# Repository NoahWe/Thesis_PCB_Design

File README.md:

# Experiment
This repository contains the PCB designs for a pressure sensor array using BMP581 sensors which will be used during an experiment as part of my MSc thesis. The experiment aims to determine the pressure distribution over a wing, located behind tilting rotors. The sensor array is specifically aimed at the vehicle designed by Alessandro Mancinelli (https://doi.org/10.1109/ICUAS54217.2022.9836063), and is supposed to resolve some of the problems experienced using tilt-rotors to roll.

## How to get started
1. Clone the repository
2. Open one of the KiCad project files (.kicad_pro).

The mainboard is located in /Experiment_PCB/MainBoard/. The sensor strips connected to the top half of the wing are located in Experiment_PCB/SensorStrip_Top/, and finally the sensor strip connected to the bottom half of the wing are located in /Experiment_PCB/SensorStrip_Bottom/.

## Sensors
The sensor which will be used for the experiment is the BMP581: https://www.bosch-sensortec.com/products/environmental-sensors/pressure-sensors/bmp581/

The setup will have 72 pressure sensors which will be driven by a single Teensy4.1 board (https://www.pjrc.com/store/teensy41.html). The Teensy4.1 features 2 SPI buses allowing me to use a single chip select line to drive two sensors. The SPI buses will run at approximately 5 MHz.

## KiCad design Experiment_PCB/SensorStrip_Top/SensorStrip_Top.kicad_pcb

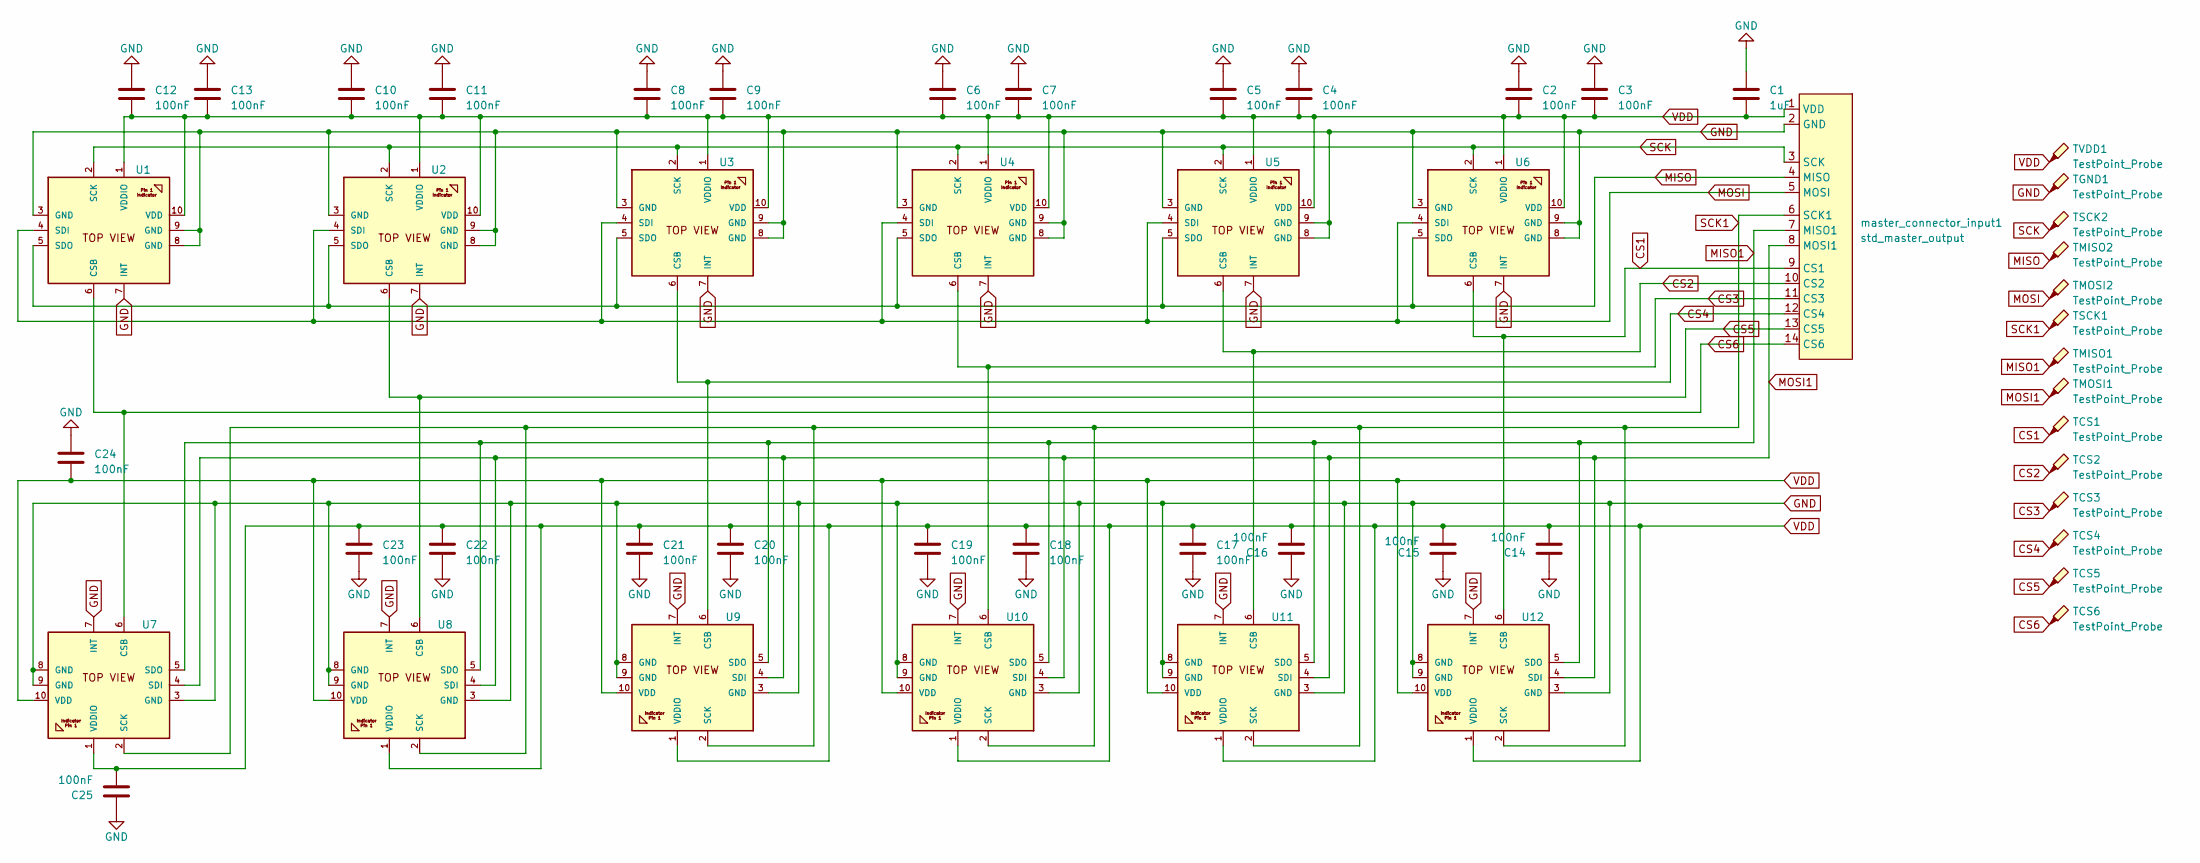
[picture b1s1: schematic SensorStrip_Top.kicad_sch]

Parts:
C1: 1uF; C_0603_1608Metric
C2, C3, C4, C5, C6, C7, C8, C9, C10, C11, C12, C13, C14, C15, C16, C17, C18, C19, C20, C21, C22, C23, C24, C25: 100nF; C_0201_0603Metric
TCS1, TCS2, TCS3, TCS4, TCS5, TCS6: TestPoint_Probe; TestPoint_Pad_1.0x1.0mm
TGND1: TestPoint_Probe; TestPoint_Pad_1.0x1.0mm
TMISO1, TMISO2: TestPoint_Probe; TestPoint_Pad_1.0x1.0mm
TMOSI1, TMOSI2: TestPoint_Probe; TestPoint_Pad_1.0x1.0mm
TSCK1, TSCK2: TestPoint_Probe; TestPoint_Pad_1.0x1.0mm
TVDD1: TestPoint_Probe; TestPoint_Pad_1.0x1.0mm
U1, U2, U3, U4, U5, U6, U7, U8, U9, U10, U11, U12: BMP581_Landing_Pattern
master_connector_input1: std_master_output; Strip_pins_top

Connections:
CS1: TCS1.1, U6.6 (CSB), U12.6 (CSB), master_connector_input1.9 (CS1)
CS2: TCS2.1, U5.6 (CSB), U11.6 (CSB), master_connector_input1.10 (CS2)
CS3: TCS3.1, U4.6 (CSB), U10.6 (CSB), master_connector_input1.11 (CS3)
CS4: TCS4.1, U3.6 (CSB), U9.6 (CSB), master_connector_input1.12 (CS4)
CS5: TCS5.1, U2.6 (CSB), U8.6 (CSB), master_connector_input1.13 (CS5)
CS6: TCS6.1, U1.6 (CSB), U7.6 (CSB), master_connector_input1.14 (CS6)
GND: C1.1, C2.1, C3.1, C4.1, C5.1, C6.1, C7.1, C8.1, C9.1, C10.1, C11.1, C12.1, C13.1, C14.1, C15.1, C16.1, C17.1, C18.1, C19.1, C20.1, C21.1, C22.1, C23.1, C24.1, C25.1, TGND1.1, U1.3 (GND), U1.7 (INT), U1.8 (GND), U1.9 (GND), U2.3 (GND), U2.7 (INT), U2.8 (GND), U2.9 (GND), U3.3 (GND), U3.7 (INT), U3.8 (GND), U3.9 (GND), U4.3 (GND), U4.7 (INT), U4.8 (GND), U4.9 (GND), U5.3 (GND), U5.7 (INT), U5.8 (GND), U5.9 (GND), U6.3 (GND), U6.7 (INT), U6.8 (GND), U6.9 (GND), U7.3 (GND), U7.7 (INT), U7.8 (GND), U7.9 (GND), U8.3 (GND), U8.7 (INT), U8.8 (GND), U8.9 (GND), U9.3 (GND), U9.7 (INT), U9.8 (GND), U9.9 (GND), U10.3 (GND), U10.7 (INT), U10.8 (GND), U10.9 (GND), U11.3 (GND), U11.7 (INT), U11.8 (GND), U11.9 (GND), U12.3 (GND), U12.7 (INT), U12.8 (GND), U12.9 (GND), master_connector_input1.2 (GND)
MISO: TMISO2.1, U1.5 (SDO), U2.5 (SDO), U3.5 (SDO), U4.5 (SDO), U5.5 (SDO), U6.5 (SDO), master_connector_input1.4 (MISO)
MISO1: TMISO1.1, U7.5 (SDO), U8.5 (SDO), U9.5 (SDO), U10.5 (SDO), U11.5 (SDO), U12.5 (SDO), master_connector_input1.7 (MISO1)
MOSI: TMOSI2.1, U1.4 (SDI), U2.4 (SDI), U3.4 (SDI), U4.4 (SDI), U5.4 (SDI), U6.4 (SDI), master_connector_input1.5 (MOSI)
MOSI1: TMOSI1.1, U7.4 (SDI), U8.4 (SDI), U9.4 (SDI), U10.4 (SDI), U11.4 (SDI), U12.4 (SDI), master_connector_input1.8 (MOSI1)
SCK: TSCK2.1, U1.2 (SCK), U2.2 (SCK), U3.2 (SCK), U4.2 (SCK), U5.2 (SCK), U6.2 (SCK), master_connector_input1.3 (SCK)
SCK1: TSCK1.1, U7.2 (SCK), U8.2 (SCK), U9.2 (SCK), U10.2 (SCK), U11.2 (SCK), U12.2 (SCK), master_connector_input1.6 (SCK1)
VDD: C1.2, C2.2, C3.2, C4.2, C5.2, C6.2, C7.2, C8.2, C9.2, C10.2, C11.2, C12.2, C13.2, C14.2, C15.2, C16.2, C17.2, C18.2, C19.2, C20.2, C21.2, C22.2, C23.2, C24.2, C25.2, TVDD1.1, U1.1 (VDDIO), U1.10 (VDD), U2.1 (VDDIO), U2.10 (VDD), U3.1 (VDDIO), U3.10 (VDD), U4.1 (VDDIO), U4.10 (VDD), U5.1 (VDDIO), U5.10 (VDD), U6.1 (VDDIO), U6.10 (VDD), U7.1 (VDDIO), U7.10 (VDD), U8.1 (VDDIO), U8.10 (VDD), U9.1 (VDDIO), U9.10 (VDD), U10.1 (VDDIO), U10.10 (VDD), U11.1 (VDDIO), U11.10 (VDD), U12.1 (VDDIO), U12.10 (VDD), master_connector_input1.1 (VDD)

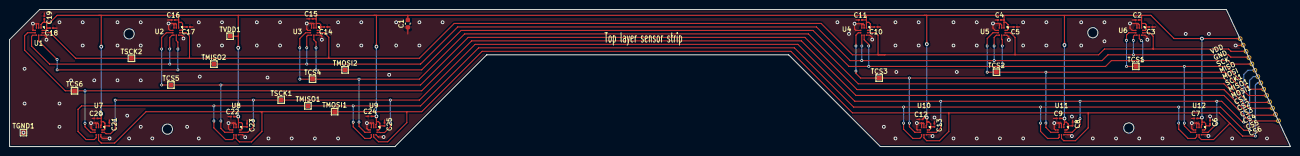
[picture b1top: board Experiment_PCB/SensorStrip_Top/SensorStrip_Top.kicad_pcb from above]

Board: 2 copper layers, 275.8 x 29.5 mm, 52 parts (0 on the bottom side), 14 nets.

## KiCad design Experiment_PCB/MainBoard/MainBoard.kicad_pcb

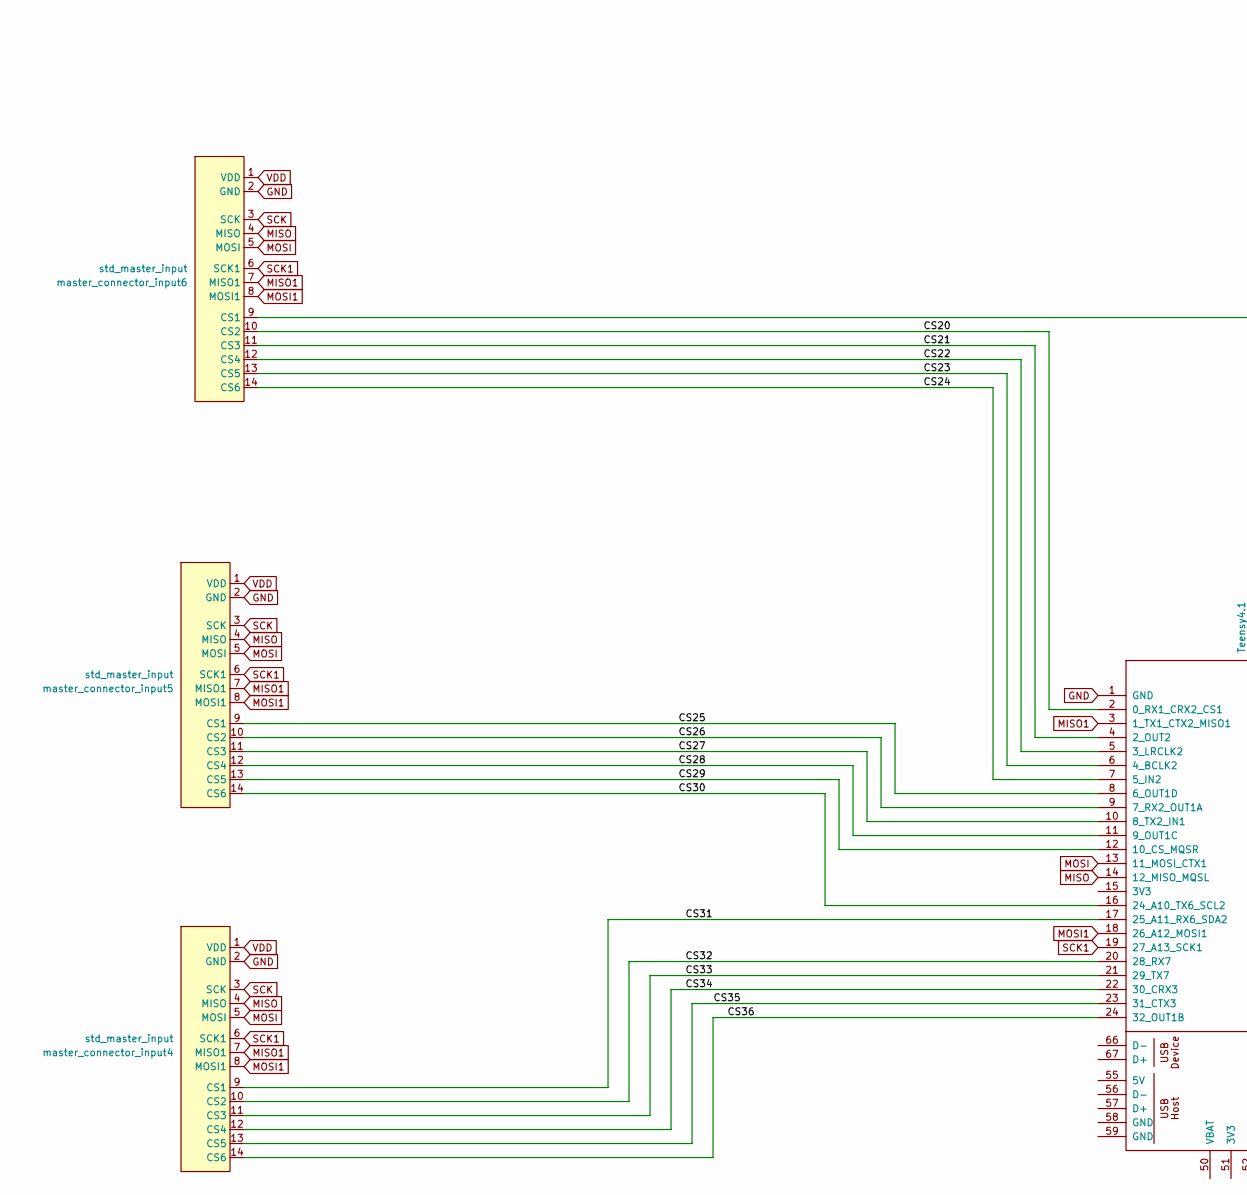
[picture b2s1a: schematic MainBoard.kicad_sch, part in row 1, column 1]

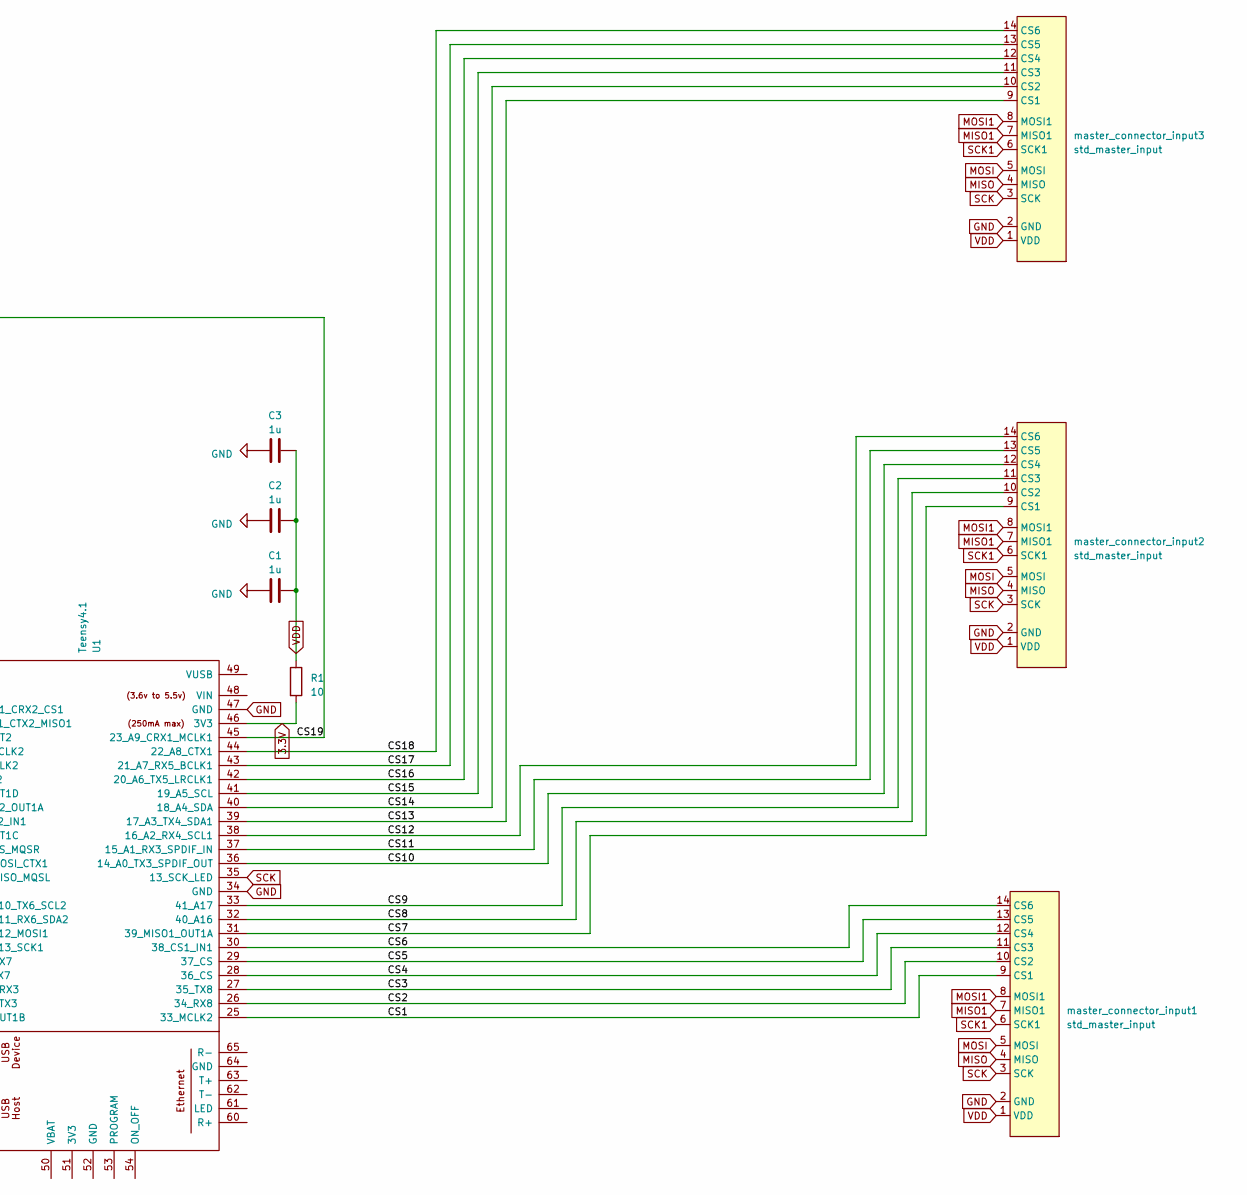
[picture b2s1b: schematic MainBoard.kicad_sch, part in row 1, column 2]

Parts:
C1, C2, C3: 1u; C_0603_1608Metric
R1: 10; R_0402_1005Metric
U1: Teensy4.1; Teensy41
master_connector_input1, master_connector_input3, master_connector_input5: std_master_input; Master_pins_top
master_connector_input2, master_connector_input4, master_connector_input6: std_master_input; Master_pins_bottom

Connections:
3.3V: R1.2, U1.46 (3V3)
/CS1: U1.25 (33_MCLK2), master_connector_input1.9 (CS1)
/CS2: U1.26 (34_RX8), master_connector_input1.10 (CS2)
/CS3: U1.27 (35_TX8), master_connector_input1.11 (CS3)
/CS4: U1.28 (36_CS), master_connector_input1.12 (CS4)
/CS5: U1.29 (37_CS), master_connector_input1.13 (CS5)
/CS6: U1.30 (38_CS1_IN1), master_connector_input1.14 (CS6)
/CS7: U1.31 (39_MISO1_OUT1A), master_connector_input2.9 (CS1)
/CS8: U1.32 (40_A16), master_connector_input2.10 (CS2)
/CS9: U1.33 (41_A17), master_connector_input2.11 (CS3)
/CS10: U1.36 (14_A0_TX3_SPDIF_OUT), master_connector_input2.12 (CS4)
/CS11: U1.37 (15_A1_RX3_SPDIF_IN), master_connector_input2.13 (CS5)
/CS12: U1.38 (16_A2_RX4_SCL1), master_connector_input2.14 (CS6)
/CS13: U1.39 (17_A3_TX4_SDA1), master_connector_input3.9 (CS1)
/CS14: U1.40 (18_A4_SDA), master_connector_input3.10 (CS2)
/CS15: U1.41 (19_A5_SCL), master_connector_input3.11 (CS3)
/CS16: U1.42 (20_A6_TX5_LRCLK1), master_connector_input3.12 (CS4)
/CS17: U1.43 (21_A7_RX5_BCLK1), master_connector_input3.13 (CS5)
/CS18: U1.44 (22_A8_CTX1), master_connector_input3.14 (CS6)
/CS19: U1.45 (23_A9_CRX1_MCLK1), master_connector_input6.9 (CS1)
/CS20: U1.2 (0_RX1_CRX2_CS1), master_connector_input6.10 (CS2)
/CS21: U1.4 (2_OUT2), master_connector_input6.11 (CS3)
/CS22: U1.5 (3_LRCLK2), master_connector_input6.12 (CS4)
/CS23: U1.6 (4_BCLK2), master_connector_input6.13 (CS5)
/CS24: U1.7 (5_IN2), master_connector_input6.14 (CS6)
/CS25: U1.8 (6_OUT1D), master_connector_input5.9 (CS1)
/CS26: U1.9 (7_RX2_OUT1A), master_connector_input5.10 (CS2)
/CS27: U1.10 (8_TX2_IN1), master_connector_input5.11 (CS3)
/CS28: U1.11 (9_OUT1C), master_connector_input5.12 (CS4)
/CS29: U1.12 (10_CS_MQSR), master_connector_input5.13 (CS5)
/CS30: U1.16 (24_A10_TX6_SCL2), master_connector_input5.14 (CS6)
/CS31: U1.17 (25_A11_RX6_SDA2), master_connector_input4.9 (CS1)
/CS32: U1.20 (28_RX7), master_connector_input4.10 (CS2)
/CS33: U1.21 (29_TX7), master_connector_input4.11 (CS3)
/CS34: U1.22 (30_CRX3), master_connector_input4.12 (CS4)
/CS35: U1.23 (31_CTX3), master_connector_input4.13 (CS5)
/CS36: U1.24 (32_OUT1B), master_connector_input4.14 (CS6)
GND: C1.1, C2.1, C3.1, U1.1 (GND), U1.34 (GND), U1.47 (GND), master_connector_input1.2 (GND), master_connector_input2.2 (GND), master_connector_input3.2 (GND), master_connector_input4.2 (GND), master_connector_input5.2 (GND), master_connector_input6.2 (GND)
MISO: U1.14 (12_MISO_MQSL), master_connector_input1.4 (MISO), master_connector_input2.4 (MISO), master_connector_input3.4 (MISO), master_connector_input4.4 (MISO), master_connector_input5.4 (MISO), master_connector_input6.4 (MISO)
MISO1: U1.3 (1_TX1_CTX2_MISO1), master_connector_input1.7 (MISO1), master_connector_input2.7 (MISO1), master_connector_input3.7 (MISO1), master_connector_input4.7 (MISO1), master_connector_input5.7 (MISO1), master_connector_input6.7 (MISO1)
MOSI: U1.13 (11_MOSI_CTX1), master_connector_input1.5 (MOSI), master_connector_input2.5 (MOSI), master_connector_input3.5 (MOSI), master_connector_input4.5 (MOSI), master_connector_input5.5 (MOSI), master_connector_input6.5 (MOSI)
MOSI1: U1.18 (26_A12_MOSI1), master_connector_input1.8 (MOSI1), master_connector_input2.8 (MOSI1), master_connector_input3.8 (MOSI1), master_connector_input4.8 (MOSI1), master_connector_input5.8 (MOSI1), master_connector_input6.8 (MOSI1)
SCK: U1.35 (13_SCK_LED), master_connector_input1.3 (SCK), master_connector_input2.3 (SCK), master_connector_input3.3 (SCK), master_connector_input4.3 (SCK), master_connector_input5.3 (SCK), master_connector_input6.3 (SCK)
SCK1: U1.19 (27_A13_SCK1), master_connector_input1.6 (SCK1), master_connector_input2.6 (SCK1), master_connector_input3.6 (SCK1), master_connector_input4.6 (SCK1), master_connector_input5.6 (SCK1), master_connector_input6.6 (SCK1)
VDD: C1.2, C2.2, C3.2, R1.1, master_connector_input1.1 (VDD), master_connector_input2.1 (VDD), master_connector_input3.1 (VDD), master_connector_input4.1 (VDD), master_connector_input5.1 (VDD), master_connector_input6.1 (VDD)

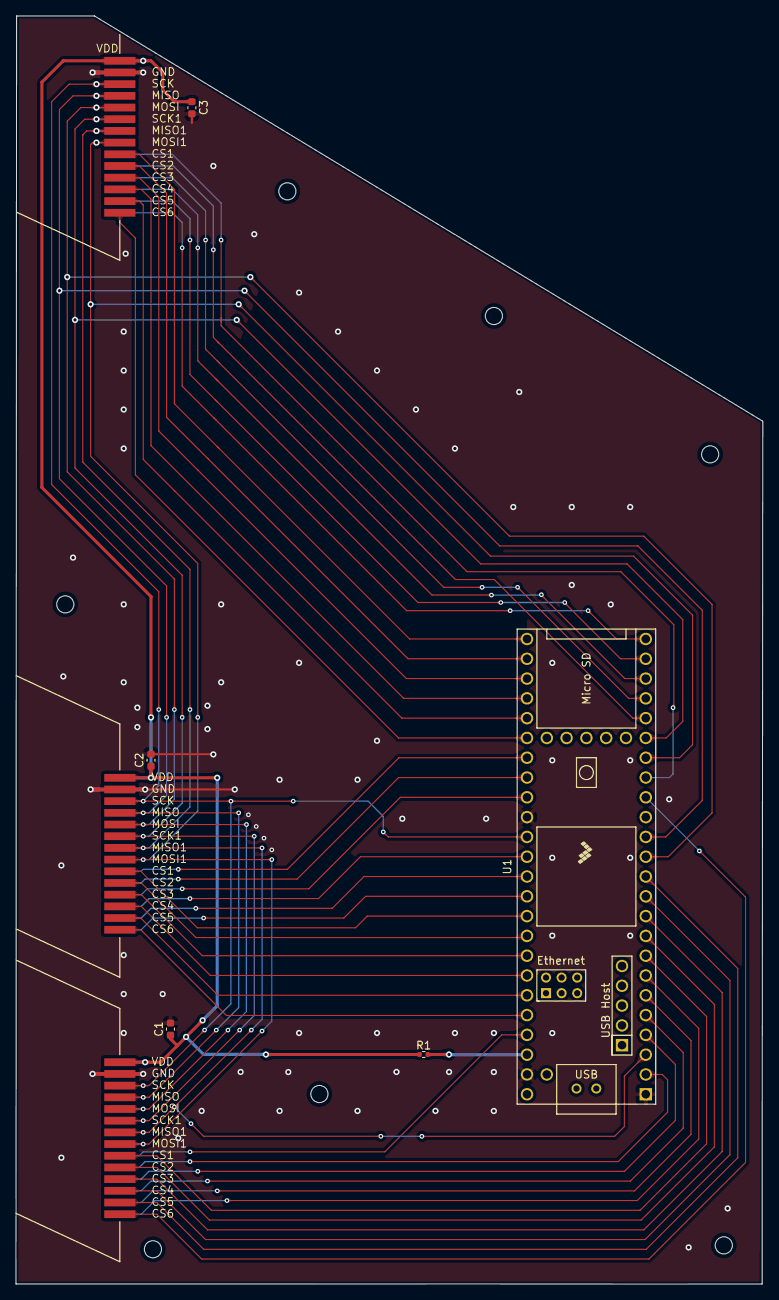
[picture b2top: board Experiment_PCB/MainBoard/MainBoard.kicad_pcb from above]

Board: 2 copper layers, 95.8 x 162.7 mm, 11 parts (0 on the bottom side), 45 nets.

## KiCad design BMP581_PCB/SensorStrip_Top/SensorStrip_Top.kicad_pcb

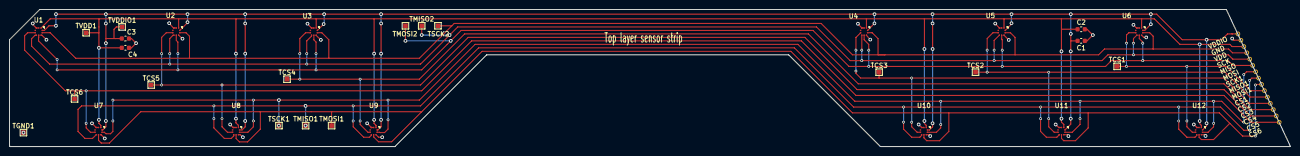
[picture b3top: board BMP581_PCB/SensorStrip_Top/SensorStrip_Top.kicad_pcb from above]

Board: 2 copper layers, 275.8 x 29.5 mm, 32 parts (0 on the bottom side), 15 nets.

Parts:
C1, C2, C3, C4: 470nF; C_0603_1608Metric
TCS1, TCS2, TCS3, TCS4, TCS5, TCS6: TestPoint_Probe; TestPoint_Pad_1.0x1.0mm
TGND1: TestPoint_Probe; TestPoint_Pad_1.0x1.0mm
TMISO1, TMISO2: TestPoint_Probe; TestPoint_Pad_1.0x1.0mm
TMOSI1, TMOSI2: TestPoint_Probe; TestPoint_Pad_1.0x1.0mm
TSCK1, TSCK2: TestPoint_Probe; TestPoint_Pad_1.0x1.0mm
TVDD1: TestPoint_Probe; TestPoint_Pad_1.0x1.0mm
TVDDIO1: TestPoint_Probe; TestPoint_Pad_1.0x1.0mm
TopConnector1: std_master_output; Strip_pins_top
U1, U2, U3, U4, U5, U6, U7, U8, U9, U10, U11, U12: BMP581_Landing_Pattern

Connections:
CS1: TCS1.1, TopConnector1.10 (CS1), U6.6 (CSB), U12.6 (CSB)
CS2: TCS2.1, TopConnector1.11 (CS2), U5.6 (CSB), U11.6 (CSB)
CS3: TCS3.1, TopConnector1.12 (CS3), U4.6 (CSB), U10.6 (CSB)
CS4: TCS4.1, TopConnector1.13 (CS4), U3.6 (CSB), U9.6 (CSB)
CS5: TCS5.1, TopConnector1.14 (CS5), U2.6 (CSB), U8.6 (CSB)
CS6: TCS6.1, TopConnector1.15 (CS6), U1.6 (CSB), U7.6 (CSB)
GND: C1.1, C2.1, C3.1, C4.1, TGND1.1, TopConnector1.2 (GND), U1.3 (GND), U1.8 (GND), U1.9 (GND), U2.3 (GND), U2.8 (GND), U2.9 (GND), U3.3 (GND), U3.8 (GND), U3.9 (GND), U4.3 (GND), U4.8 (GND), U4.9 (GND), U5.3 (GND), U5.8 (GND), U5.9 (GND), U6.3 (GND), U6.8 (GND), U6.9 (GND), U7.3 (GND), U7.8 (GND), U7.9 (GND), U8.3 (GND), U8.8 (GND), U8.9 (GND), U9.3 (GND), U9.8 (GND), U9.9 (GND), U10.3 (GND), U10.8 (GND), U10.9 (GND), U11.3 (GND), U11.8 (GND), U11.9 (GND), U12.3 (GND), U12.8 (GND), U12.9 (GND)
MISO: TMISO2.1, TopConnector1.5 (MISO), U1.5 (SDO), U2.5 (SDO), U3.5 (SDO), U4.5 (SDO), U5.5 (SDO), U6.5 (SDO)
MISO1: TMISO1.1, TopConnector1.8 (MISO1), U7.5 (SDO), U8.5 (SDO), U9.5 (SDO), U10.5 (SDO), U11.5 (SDO), U12.5 (SDO)
MOSI: TMOSI2.1, TopConnector1.6 (MOSI), U1.4 (SDI), U2.4 (SDI), U3.4 (SDI), U4.4 (SDI), U5.4 (SDI), U6.4 (SDI)
MOSI1: TMOSI1.1, TopConnector1.9 (MOSI1), U7.4 (SDI), U8.4 (SDI), U9.4 (SDI), U10.4 (SDI), U11.4 (SDI), U12.4 (SDI)
SCK: TSCK2.1, TopConnector1.4 (SCK), U1.2 (SCK), U2.2 (SCK), U3.2 (SCK), U4.2 (SCK), U5.2 (SCK), U6.2 (SCK)
SCK1: TSCK1.1, TopConnector1.7 (SCK1), U7.2 (SCK), U8.2 (SCK), U9.2 (SCK), U10.2 (SCK), U11.2 (SCK), U12.2 (SCK)
VDD: C2.2, C4.2, TVDD1.1, TopConnector1.3 (VDD), U1.10 (VDD), U2.10 (VDD), U3.10 (VDD), U4.10 (VDD), U5.10 (VDD), U6.10 (VDD), U7.10 (VDD), U8.10 (VDD), U9.10 (VDD), U10.10 (VDD), U11.10 (VDD), U12.10 (VDD)
VDDIO: C1.2, C3.2, TVDDIO1.1, TopConnector1.1 (VDDIO), U1.1 (VDDIO), U2.1 (VDDIO), U3.1 (VDDIO), U4.1 (VDDIO), U5.1 (VDDIO), U6.1 (VDDIO), U7.1 (VDDIO), U8.1 (VDDIO), U9.1 (VDDIO), U10.1 (VDDIO), U11.1 (VDDIO), U12.1 (VDDIO)

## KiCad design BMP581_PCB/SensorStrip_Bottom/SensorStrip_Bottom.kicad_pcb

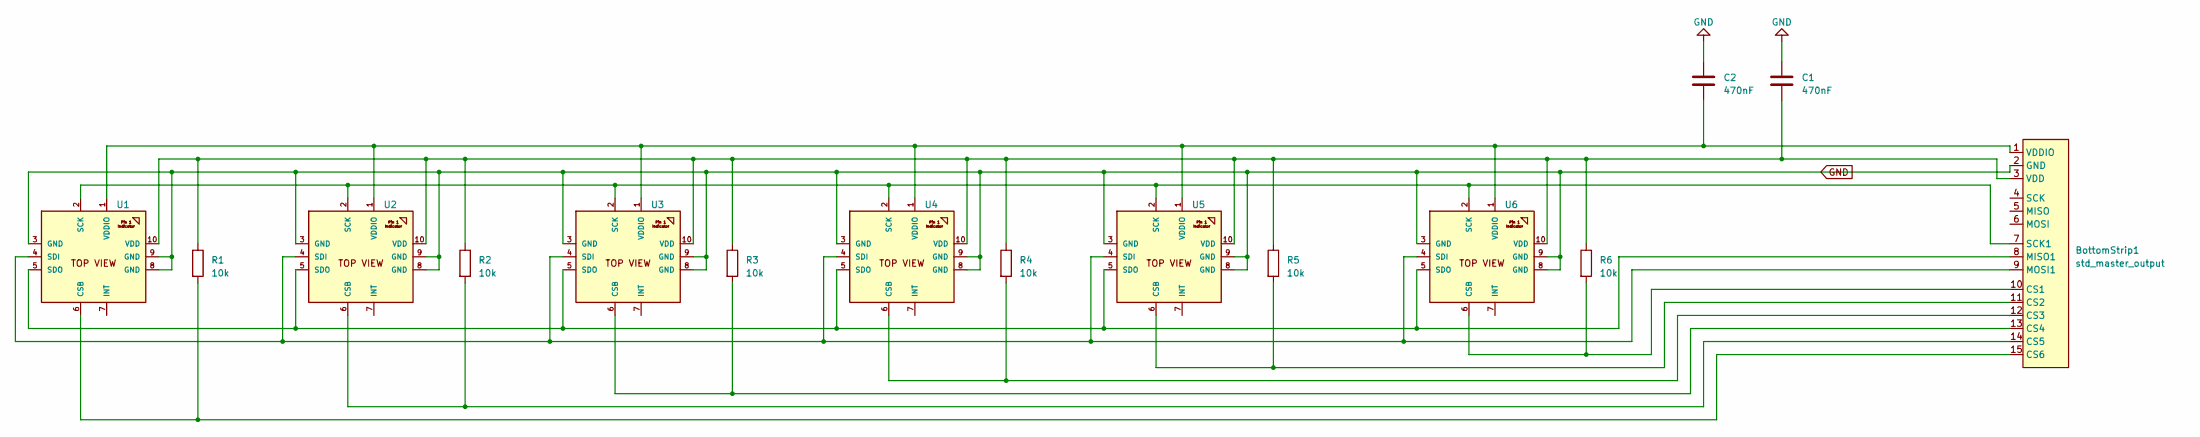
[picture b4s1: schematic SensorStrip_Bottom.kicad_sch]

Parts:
BottomStrip1: std_master_output; Strip_pins_bottom
C1, C2: 470nF; C_0603_1608Metric
R1, R2, R3, R4, R5, R6: 10k; R_0402_1005Metric
U1, U2, U3, U4, U5, U6: BMP581_Landing_Pattern

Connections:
GND: BottomStrip1.2 (GND), C1.1, C2.1, U1.3 (GND), U1.8 (GND), U1.9 (GND), U2.3 (GND), U2.8 (GND), U2.9 (GND), U3.3 (GND), U3.8 (GND), U3.9 (GND), U4.3 (GND), U4.8 (GND), U4.9 (GND), U5.3 (GND), U5.8 (GND), U5.9 (GND), U6.3 (GND), U6.8 (GND), U6.9 (GND)
unnamed: BottomStrip1.10 (CS1), R6.2, U6.6 (CSB)
unnamed: BottomStrip1.11 (CS2), R5.2, U5.6 (CSB)
unnamed: BottomStrip1.12 (CS3), R4.2, U4.6 (CSB)
unnamed: BottomStrip1.13 (CS4), R3.2, U3.6 (CSB)
unnamed: BottomStrip1.14 (CS5), R2.2, U2.6 (CSB)
unnamed: BottomStrip1.15 (CS6), R1.2, U1.6 (CSB)
unnamed: BottomStrip1.8 (MISO1), U1.5 (SDO), U2.5 (SDO), U3.5 (SDO), U4.5 (SDO), U5.5 (SDO), U6.5 (SDO)
unnamed: BottomStrip1.9 (MOSI1), U1.4 (SDI), U2.4 (SDI), U3.4 (SDI), U4.4 (SDI), U5.4 (SDI), U6.4 (SDI)
unnamed: BottomStrip1.7 (SCK1), U1.2 (SCK), U2.2 (SCK), U3.2 (SCK), U4.2 (SCK), U5.2 (SCK), U6.2 (SCK)
unnamed: BottomStrip1.3 (VDD), C1.2, R1.1, R2.1, R3.1, R4.1, R5.1, R6.1, U1.10 (VDD), U2.10 (VDD), U3.10 (VDD), U4.10 (VDD), U5.10 (VDD), U6.10 (VDD)
unnamed: BottomStrip1.1 (VDDIO), C2.2, U1.1 (VDDIO), U2.1 (VDDIO), U3.1 (VDDIO), U4.1 (VDDIO), U5.1 (VDDIO), U6.1 (VDDIO)

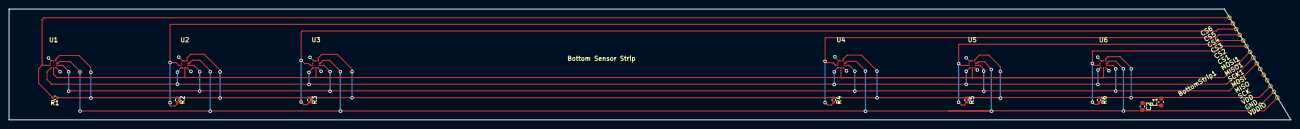
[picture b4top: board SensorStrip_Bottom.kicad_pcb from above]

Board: 2 copper layers, 289.3 x 25.0 mm, 15 parts (0 on the bottom side), 12 nets.

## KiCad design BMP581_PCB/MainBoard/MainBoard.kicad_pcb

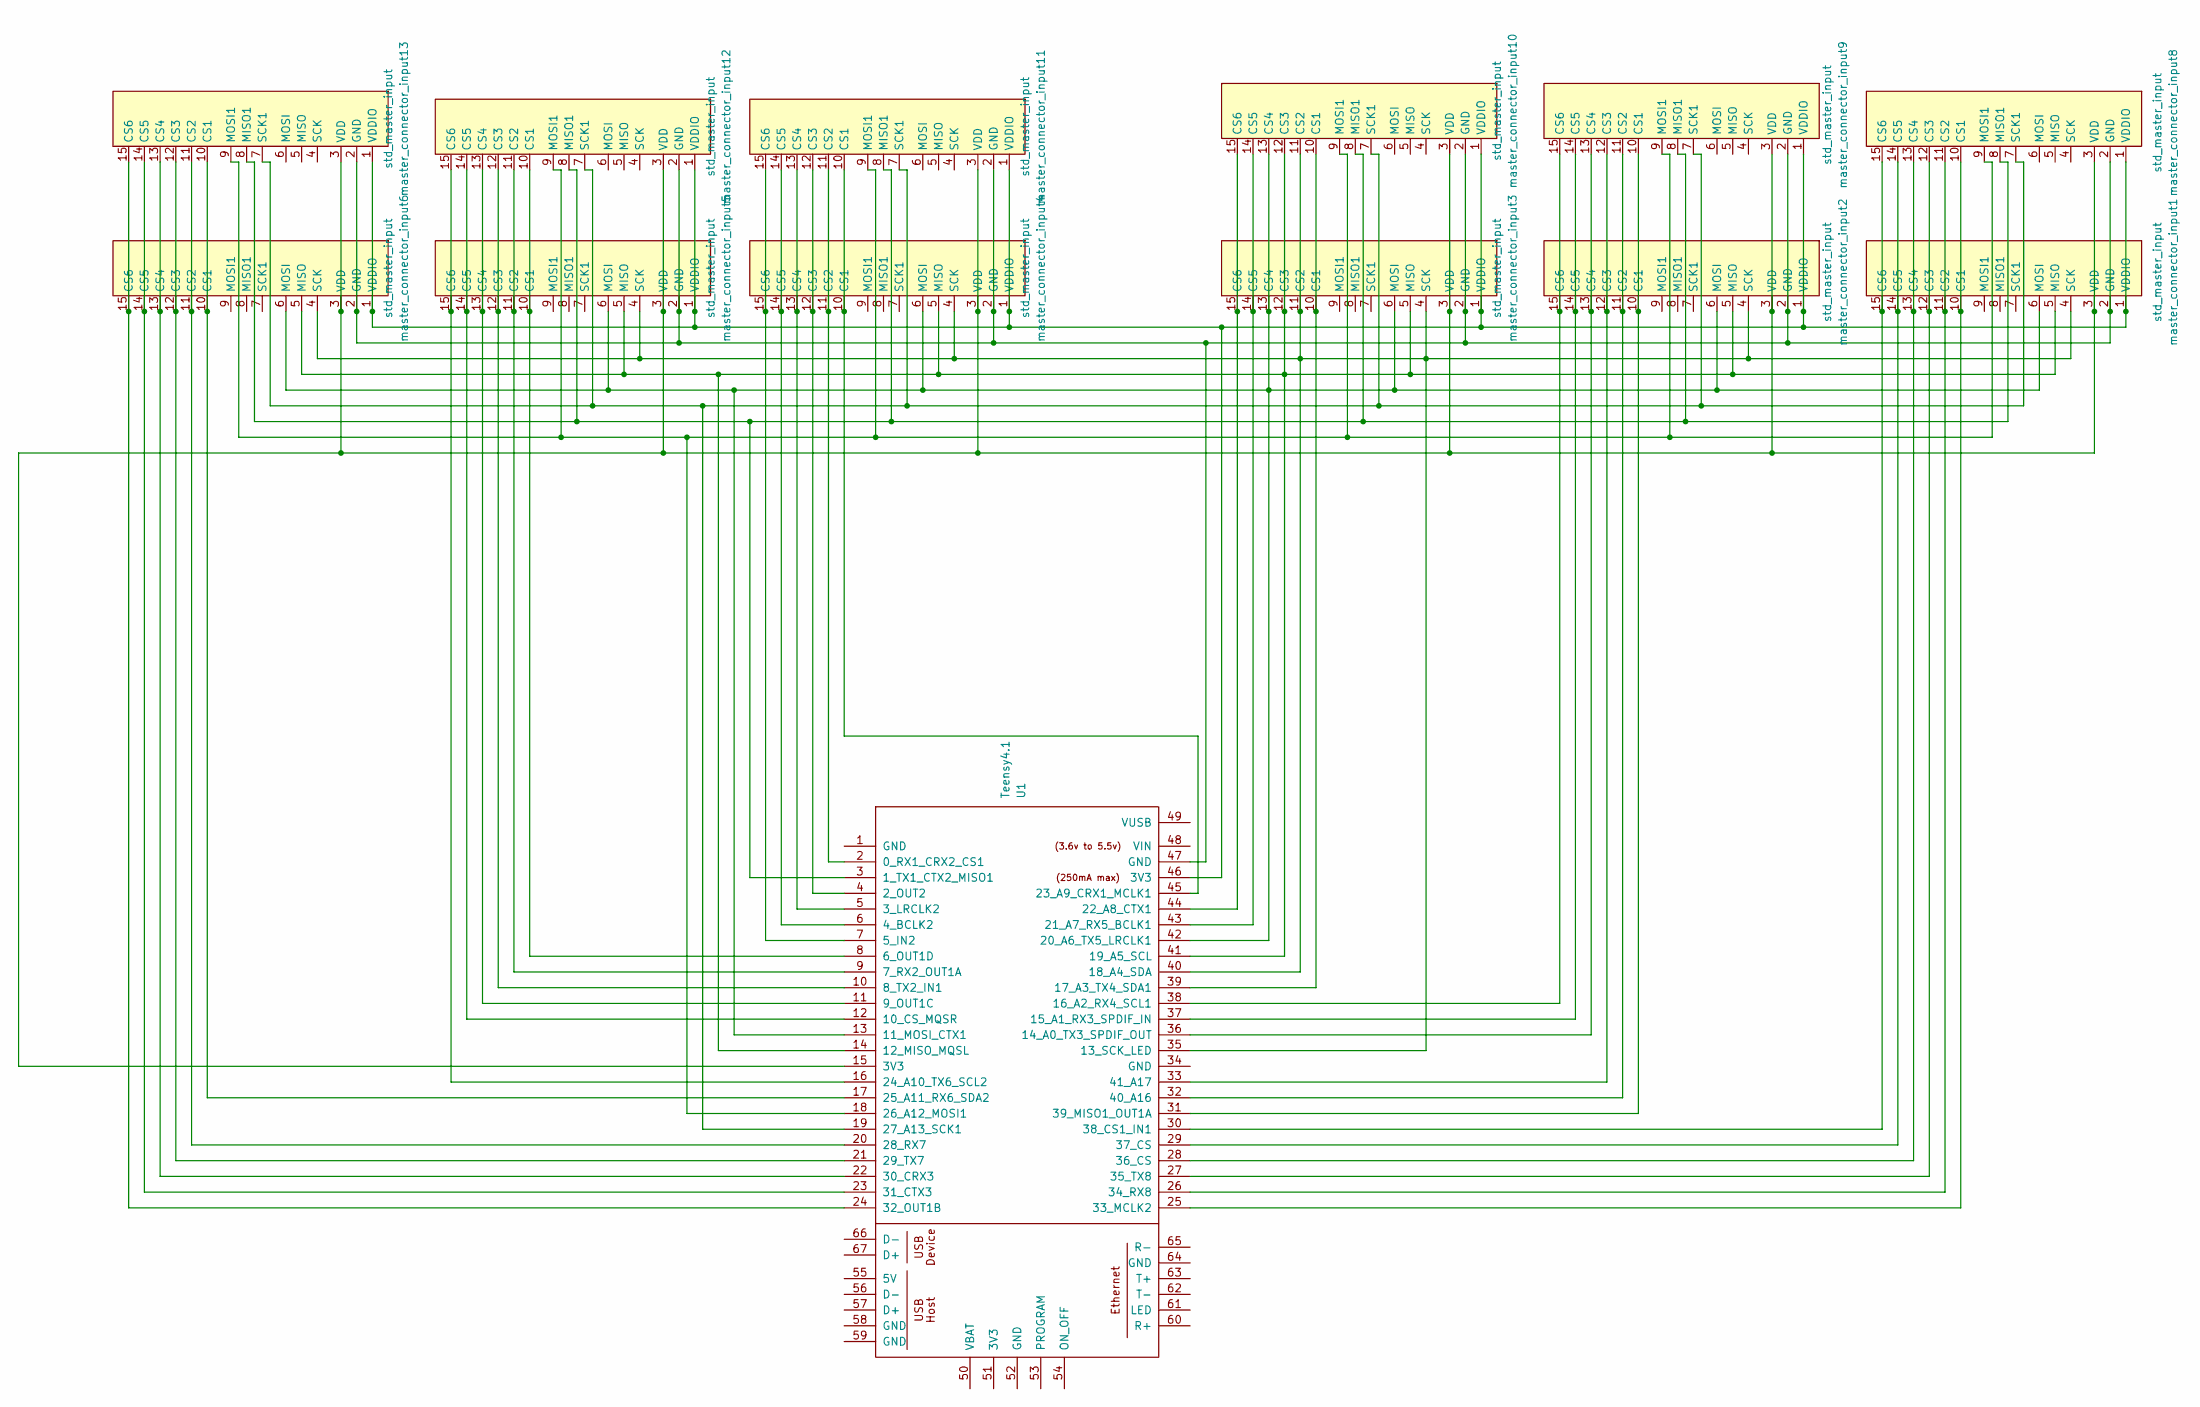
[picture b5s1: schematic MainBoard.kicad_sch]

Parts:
U1: Teensy4.1; Teensy41
master_connector_input1, master_connector_input2, master_connector_input3, master_connector_input4, master_connector_input5, master_connector_input6: std_master_input; Master_pins_top
master_connector_input8, master_connector_input9, master_connector_input10, master_connector_input11, master_connector_input12, master_connector_input13: std_master_input; Master_pins_bottom

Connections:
unnamed: U1.2 (0_RX1_CRX2_CS1), master_connector_input4.11 (CS2), master_connector_input11.11 (CS2)
unnamed: U1.3 (1_TX1_CTX2_MISO1), master_connector_input8.8 (MISO1), master_connector_input9.8 (MISO1), master_connector_input10.8 (MISO1), master_connector_input11.8 (MISO1), master_connector_input12.8 (MISO1), master_connector_input13.8 (MISO1)
unnamed: U1.4 (2_OUT2), master_connector_input4.12 (CS3), master_connector_input11.12 (CS3)
unnamed: U1.5 (3_LRCLK2), master_connector_input4.13 (CS4), master_connector_input11.13 (CS4)
unnamed: U1.6 (4_BCLK2), master_connector_input4.14 (CS5), master_connector_input11.14 (CS5)
unnamed: U1.7 (5_IN2), master_connector_input4.15 (CS6), master_connector_input11.15 (CS6)
unnamed: U1.8 (6_OUT1D), master_connector_input5.10 (CS1), master_connector_input12.10 (CS1)
unnamed: U1.9 (7_RX2_OUT1A), master_connector_input5.11 (CS2), master_connector_input12.11 (CS2)
unnamed: U1.10 (8_TX2_IN1), master_connector_input5.12 (CS3), master_connector_input12.12 (CS3)
unnamed: U1.11 (9_OUT1C), master_connector_input5.13 (CS4), master_connector_input12.13 (CS4)
unnamed: U1.12 (10_CS_MQSR), master_connector_input5.14 (CS5), master_connector_input12.14 (CS5)
unnamed: U1.13 (11_MOSI_CTX1), U1.42 (20_A6_TX5_LRCLK1), master_connector_input1.6 (MOSI), master_connector_input2.6 (MOSI), master_connector_input3.6 (MOSI), master_connector_input3.13 (CS4), master_connector_input4.6 (MOSI), master_connector_input5.6 (MOSI), master_connector_input6.6 (MOSI), master_connector_input10.13 (CS4)
unnamed: U1.14 (12_MISO_MQSL), U1.41 (19_A5_SCL), master_connector_input1.5 (MISO), master_connector_input2.5 (MISO), master_connector_input3.5 (MISO), master_connector_input3.12 (CS3), master_connector_input4.5 (MISO), master_connector_input5.5 (MISO), master_connector_input6.5 (MISO), master_connector_input10.12 (CS3)
unnamed: U1.35 (13_SCK_LED), U1.40 (18_A4_SDA), master_connector_input1.4 (SCK), master_connector_input2.4 (SCK), master_connector_input3.4 (SCK), master_connector_input3.11 (CS2), master_connector_input4.4 (SCK), master_connector_input5.4 (SCK), master_connector_input6.4 (SCK), master_connector_input10.11 (CS2)
unnamed: U1.36 (14_A0_TX3_SPDIF_OUT), master_connector_input2.13 (CS4), master_connector_input9.13 (CS4)
unnamed: U1.37 (15_A1_RX3_SPDIF_IN), master_connector_input2.14 (CS5), master_connector_input9.14 (CS5)
unnamed: U1.38 (16_A2_RX4_SCL1), master_connector_input2.15 (CS6), master_connector_input9.15 (CS6)
unnamed: U1.39 (17_A3_TX4_SDA1), master_connector_input3.10 (CS1), master_connector_input10.10 (CS1)
unnamed: U1.43 (21_A7_RX5_BCLK1), master_connector_input3.14 (CS5), master_connector_input10.14 (CS5)
unnamed: U1.44 (22_A8_CTX1), master_connector_input3.15 (CS6), master_connector_input10.15 (CS6)
unnamed: U1.45 (23_A9_CRX1_MCLK1), master_connector_input4.10 (CS1), master_connector_input11.10 (CS1)
unnamed: U1.16 (24_A10_TX6_SCL2), master_connector_input5.15 (CS6), master_connector_input12.15 (CS6)
unnamed: U1.17 (25_A11_RX6_SDA2), master_connector_input6.10 (CS1), master_connector_input13.10 (CS1)
unnamed: U1.18 (26_A12_MOSI1), master_connector_input8.9 (MOSI1), master_connector_input9.9 (MOSI1), master_connector_input10.9 (MOSI1), master_connector_input11.9 (MOSI1), master_connector_input12.9 (MOSI1), master_connector_input13.9 (MOSI1)
unnamed: U1.19 (27_A13_SCK1), master_connector_input8.7 (SCK1), master_connector_input9.7 (SCK1), master_connector_input10.7 (SCK1), master_connector_input11.7 (SCK1), master_connector_input12.7 (SCK1), master_connector_input13.7 (SCK1)
unnamed: U1.20 (28_RX7), master_connector_input6.11 (CS2), master_connector_input13.11 (CS2)
unnamed: U1.21 (29_TX7), master_connector_input6.12 (CS3), master_connector_input13.12 (CS3)
unnamed: U1.22 (30_CRX3), master_connector_input6.13 (CS4), master_connector_input13.13 (CS4)
unnamed: U1.23 (31_CTX3), master_connector_input6.14 (CS5), master_connector_input13.14 (CS5)
unnamed: U1.24 (32_OUT1B), master_connector_input6.15 (CS6), master_connector_input13.15 (CS6)
unnamed: U1.25 (33_MCLK2), master_connector_input1.10 (CS1), master_connector_input8.10 (CS1)
unnamed: U1.26 (34_RX8), master_connector_input1.11 (CS2), master_connector_input8.11 (CS2)
unnamed: U1.27 (35_TX8), master_connector_input1.12 (CS3), master_connector_input8.12 (CS3)
unnamed: U1.28 (36_CS), master_connector_input1.13 (CS4), master_connector_input8.13 (CS4)
unnamed: U1.29 (37_CS), master_connector_input1.14 (CS5), master_connector_input8.14 (CS5)
unnamed: U1.30 (38_CS1_IN1), master_connector_input1.15 (CS6), master_connector_input8.15 (CS6)
unnamed: U1.31 (39_MISO1_OUT1A), master_connector_input2.10 (CS1), master_connector_input9.10 (CS1)
unnamed: U1.32 (40_A16), master_connector_input2.11 (CS2), master_connector_input9.11 (CS2)
unnamed: U1.33 (41_A17), master_connector_input2.12 (CS3), master_connector_input9.12 (CS3)
unnamed: U1.47 (GND), master_connector_input1.2 (GND), master_connector_input2.2 (GND), master_connector_input3.2 (GND), master_connector_input4.2 (GND), master_connector_input5.2 (GND), master_connector_input6.2 (GND), master_connector_input8.2 (GND), master_connector_input9.2 (GND), master_connector_input10.2 (GND), master_connector_input11.2 (GND), master_connector_input12.2 (GND), master_connector_input13.2 (GND)
unnamed: U1.15 (3V3), master_connector_input1.3 (VDD), master_connector_input2.3 (VDD), master_connector_input3.3 (VDD), master_connector_input4.3 (VDD), master_connector_input5.3 (VDD), master_connector_input6.3 (VDD), master_connector_input8.3 (VDD), master_connector_input9.3 (VDD), master_connector_input10.3 (VDD), master_connector_input11.3 (VDD), master_connector_input12.3 (VDD), master_connector_input13.3 (VDD)
unnamed: U1.46 (3V3), master_connector_input1.1 (VDDIO), master_connector_input2.1 (VDDIO), master_connector_input3.1 (VDDIO), master_connector_input4.1 (VDDIO), master_connector_input5.1 (VDDIO), master_connector_input6.1 (VDDIO), master_connector_input8.1 (VDDIO), master_connector_input9.1 (VDDIO), master_connector_input10.1 (VDDIO), master_connector_input11.1 (VDDIO), master_connector_input12.1 (VDDIO), master_connector_input13.1 (VDDIO)
